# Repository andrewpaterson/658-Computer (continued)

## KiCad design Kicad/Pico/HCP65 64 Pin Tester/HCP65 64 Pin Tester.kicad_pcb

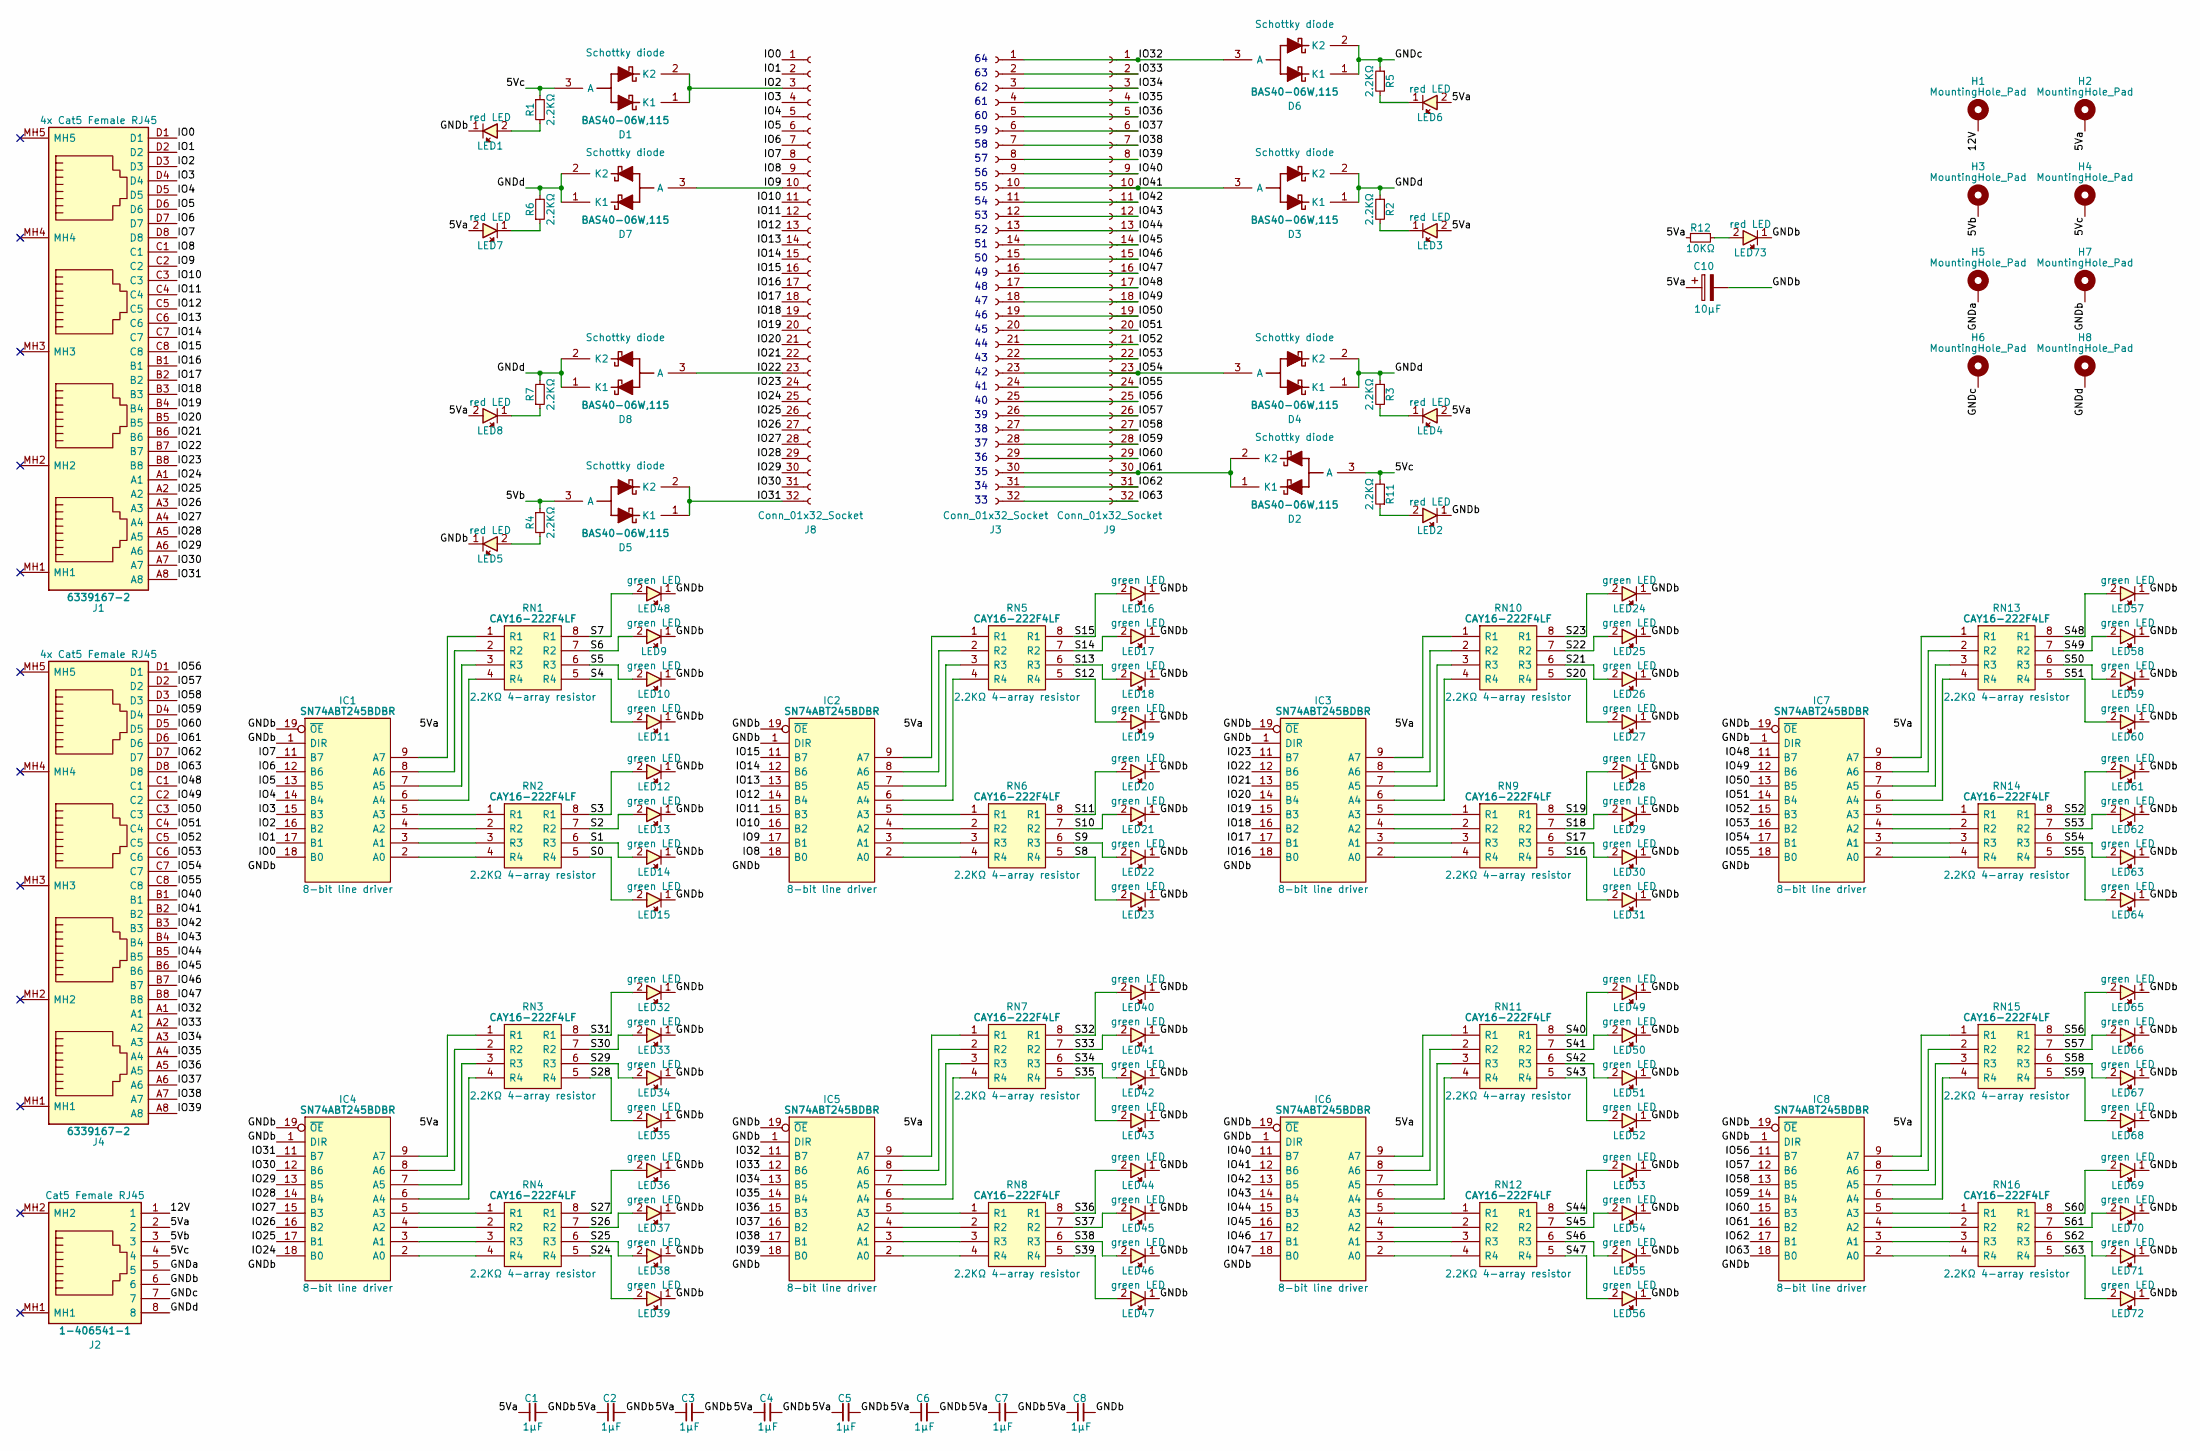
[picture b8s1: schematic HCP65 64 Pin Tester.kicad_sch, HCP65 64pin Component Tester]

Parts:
C1, C2, C3, C4, C5, C6, C7, C8: 1μF; C_0805
C10: 10μF; CP_Radial_D4.0mm_P2.00mm
D1, D2, D3, D4, D5, D6, D7, D8: BAS40-06W,115; SOT65P210X110-3N; Manufacturer_Part_Number BAS40-06W,115; Mouser Part Number 771-BAS40-06W115
H1, H2, H3, H4, H5, H6, H7, H8: MountingHole_Pad; MountingHole_3.2mm_M3_Pad
IC1, IC2, IC3, IC4, IC5, IC6, IC7, IC8: SN74ABT245BDBR; SOP65P780X200-20N; Manufacturer_Part_Number SN74ABT245BDBR; Mouser Part Number 595-SN74ABT245BDBR
J1, J4: 6339167-2; 63391672; Manufacturer_Part_Number 6339167-2; Mouser Part Number 571-6339167-2
J2: 1-406541-1; 1-406541-1_1; Manufacturer_Part_Number 1-406541-1; Mouser Part Number 571-1-406541-1
J3, J8, J9: Conn_01x32_Socket; PinSocket_1x32_P2.54mm_Vertical
LED1, LED2, LED3, LED4, LED5, LED6, LED7, LED8, LED73: 150224SS73100; 150224SS73100A; Manufacturer_Part_Number 150224SS73100; Mouser Part Number 710-150224SS73100
LED9, LED10, LED11, LED12, LED13, LED14, LED15, LED16, LED17, LED18, LED19, LED20, LED21, LED22, LED23, LED24, LED25, LED26, LED27, LED28, LED29, LED30, LED31, LED32, LED33, LED34, LED35, LED36, LED37, LED38, LED39, LED40, LED41, LED42, LED43, LED44, LED45, LED46, LED47, LED48, LED49, LED50, LED51, LED52, LED53, LED54, LED55, LED56, LED57, LED58, LED59, LED60, LED61, LED62, LED63, LED64, LED65, LED66, LED67, LED68, LED69, LED70, LED71, LED72: 150224VS73100A; Manufacturer_Part_Number 150224VS73100A; Mouser Part Number 710-150224VS73100A
R1, R2, R3, R4, R5, R6, R7, R11: 2.2KΩ; R_0805
R12: 10KΩ; R_0805
RN1, RN2, RN3, RN4, RN5, RN6, RN7, RN8, RN9, RN10, RN11, RN12, RN13, RN14, RN15, RN16: CAY16-222F4LF; CAY16-J4; Manufacturer_Part_Number CAY16-222F4LF; Mouser Part Number 652-CAY16-2201F4LF

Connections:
/5Va: C1.1, C2.1, C3.1, C4.1, C5.1, C6.1, C7.1, C8.1, C10.1, H2.1, IC1.20 (5V), IC2.20 (5V), IC3.20 (5V), IC4.20 (5V), IC5.20 (5V), IC6.20 (5V), IC7.20 (5V), IC8.20 (5V), J2.2, LED3.2, LED4.2, LED6.2, LED7.2, LED8.2, R12.1
/5Vb: D5.3 (A), H3.1, J2.3, R4.1
/5Vc: D1.3 (A), D2.3 (A), H4.1, J2.4, R1.1, R11.2
/12V: H1.1, J2.1
/GNDa: H5.1, J2.5
/GNDb: C1.2, C2.2, C3.2, C4.2, C5.2, C6.2, C7.2, C8.2, C10.2, H7.1, IC1.1 (DIR), IC1.10 (GND), IC1.19 (~OE), IC2.1 (DIR), IC2.10 (GND), IC2.19 (~OE), IC3.1 (DIR), IC3.10 (GND), IC3.19 (~OE), IC4.1 (DIR), IC4.10 (GND), IC4.19 (~OE), IC5.1 (DIR), IC5.10 (GND), IC5.19 (~OE), IC6.1 (DIR), IC6.10 (GND), IC6.19 (~OE), IC7.1 (DIR), IC7.10 (GND), IC7.19 (~OE), IC8.1 (DIR), IC8.10 (GND), IC8.19 (~OE), J2.6, LED1.1, LED2.1, LED5.1, LED9.1, LED10.1, LED11.1, LED12.1, LED13.1, LED14.1, LED15.1, LED16.1, LED17.1, LED18.1, LED19.1, LED20.1, LED21.1, LED22.1, LED23.1, LED24.1, LED25.1, LED26.1, LED27.1, LED28.1, LED29.1, LED30.1, LED31.1, LED32.1, LED33.1, LED34.1, LED35.1, LED36.1, LED37.1, LED38.1, LED39.1, LED40.1, LED41.1, LED42.1, LED43.1, LED44.1, LED45.1, LED46.1, LED47.1, LED48.1, LED49.1, LED50.1, LED51.1, LED52.1, LED53.1, LED54.1, LED55.1, LED56.1, LED57.1, LED58.1, LED59.1, LED60.1, LED61.1, LED62.1, LED63.1, LED64.1, LED65.1, LED66.1, LED67.1, LED68.1, LED69.1, LED70.1, LED71.1, LED72.1, LED73.1
/GNDc: D6.1 (K1), D6.2 (K2), H6.1, J2.7, R5.1
/GNDd: D3.1 (K1), D3.2 (K2), D4.1 (K1), D4.2 (K2), D7.1 (K1), D7.2 (K2), D8.1 (K1), D8.2 (K2), H8.1, J2.8, R2.1, R3.1, R6.2, R7.2
/IO0: IC1.18 (B0), J1.D1, J8.1
/IO1: IC1.17 (B1), J1.D2, J8.2
/IO2: D1.1 (K1), D1.2 (K2), IC1.16 (B2), J1.D3, J8.3
/IO3: IC1.15 (B3), J1.D4, J8.4
/IO4: IC1.14 (B4), J1.D5, J8.5
/IO5: IC1.13 (B5), J1.D6, J8.6
/IO6: IC1.12 (B6), J1.D7, J8.7
/IO7: IC1.11 (B7), J1.D8, J8.8
/IO8: IC2.18 (B0), J1.C1, J8.9
/IO9: D7.3 (A), IC2.17 (B1), J1.C2, J8.10
/IO10: IC2.16 (B2), J1.C3, J8.11
/IO11: IC2.15 (B3), J1.C4, J8.12
/IO12: IC2.14 (B4), J1.C5, J8.13
/IO13: IC2.13 (B5), J1.C6, J8.14
/IO14: IC2.12 (B6), J1.C7, J8.15
/IO15: IC2.11 (B7), J1.C8, J8.16
/IO16: IC3.18 (B0), J1.B1, J8.17
/IO17: IC3.17 (B1), J1.B2, J8.18
/IO18: IC3.16 (B2), J1.B3, J8.19
/IO19: IC3.15 (B3), J1.B4, J8.20
/IO20: IC3.14 (B4), J1.B5, J8.21
/IO21: IC3.13 (B5), J1.B6, J8.22
/IO22: D8.3 (A), IC3.12 (B6), J1.B7, J8.23
/IO23: IC3.11 (B7), J1.B8, J8.24
/IO24: IC4.18 (B0), J1.A1, J8.25
/IO25: IC4.17 (B1), J1.A2, J8.26
/IO26: IC4.16 (B2), J1.A3, J8.27
/IO27: IC4.15 (B3), J1.A4, J8.28
/IO28: IC4.14 (B4), J1.A5, J8.29
/IO29: IC4.13 (B5), J1.A6, J8.30
/IO30: IC4.12 (B6), J1.A7, J8.31
/IO31: D5.1 (K1), D5.2 (K2), IC4.11 (B7), J1.A8, J8.32
/IO32: D6.3 (A), IC5.11 (B7), J3.1, J4.A1, J9.1
/IO33: IC5.12 (B6), J3.2, J4.A2, J9.2
/IO34: IC5.13 (B5), J3.3, J4.A3, J9.3
/IO35: IC5.14 (B4), J3.4, J4.A4, J9.4
/IO36: IC5.15 (B3), J3.5, J4.A5, J9.5
/IO37: IC5.16 (B2), J3.6, J4.A6, J9.6
/IO38: IC5.17 (B1), J3.7, J4.A7, J9.7
/IO39: IC5.18 (B0), J3.8, J4.A8, J9.8
/IO40: IC6.11 (B7), J3.9, J4.B1, J9.9
/IO41: D3.3 (A), IC6.12 (B6), J3.10, J4.B2, J9.10
/IO42: IC6.13 (B5), J3.11, J4.B3, J9.11
/IO43: IC6.14 (B4), J3.12, J4.B4, J9.12
/IO44: IC6.15 (B3), J3.13, J4.B5, J9.13
/IO45: IC6.16 (B2), J3.14, J4.B6, J9.14
/IO46: IC6.17 (B1), J3.15, J4.B7, J9.15
/IO47: IC6.18 (B0), J3.16, J4.B8, J9.16
/IO48: IC7.11 (B7), J3.17, J4.C1, J9.17
/IO49: IC7.12 (B6), J3.18, J4.C2, J9.18
/IO50: IC7.13 (B5), J3.19, J4.C3, J9.19
/IO51: IC7.14 (B4), J3.20, J4.C4, J9.20
/IO52: IC7.15 (B3), J3.21, J4.C5, J9.21
/IO53: IC7.16 (B2), J3.22, J4.C6, J9.22
/IO54: D4.3 (A), IC7.17 (B1), J3.23, J4.C7, J9.23
/IO55: IC7.18 (B0), J3.24, J4.C8, J9.24
/IO56: IC8.11 (B7), J3.25, J4.D1, J9.25
/IO57: IC8.12 (B6), J3.26, J4.D2, J9.26
/IO58: IC8.13 (B5), J3.27, J4.D3, J9.27
/IO59: IC8.14 (B4), J3.28, J4.D4, J9.28
/IO60: IC8.15 (B3), J3.29, J4.D5, J9.29
/IO61: D2.1 (K1), D2.2 (K2), IC8.16 (B2), J3.30, J4.D6, J9.30
/IO62: IC8.17 (B1), J3.31, J4.D7, J9.31
/IO63: IC8.18 (B0), J3.32, J4.D8, J9.32
/S0: LED15.2, RN2.5 (R4)
/S1: LED14.2, RN2.6 (R3)
/S2: LED13.2, RN2.7 (R2)
/S3: LED12.2, RN2.8 (R1)
/S4: LED11.2, RN1.5 (R4)
/S5: LED10.2, RN1.6 (R3)
/S6: LED9.2, RN1.7 (R2)
/S7: LED48.2, RN1.8 (R1)
/S8: LED23.2, RN6.5 (R4)
/S9: LED22.2, RN6.6 (R3)
/S10: LED21.2, RN6.7 (R2)
/S11: LED20.2, RN6.8 (R1)
/S12: LED19.2, RN5.5 (R4)
/S13: LED18.2, RN5.6 (R3)
/S14: LED17.2, RN5.7 (R2)
/S15: LED16.2, RN5.8 (R1)
/S16: LED31.2, RN9.5 (R4)
/S17: LED30.2, RN9.6 (R3)
/S18: LED29.2, RN9.7 (R2)
/S19: LED28.2, RN9.8 (R1)
/S20: LED27.2, RN10.5 (R4)
/S21: LED26.2, RN10.6 (R3)
/S22: LED25.2, RN10.7 (R2)
/S23: LED24.2, RN10.8 (R1)
/S24: LED39.2, RN4.5 (R4)
/S25: LED38.2, RN4.6 (R3)
/S26: LED37.2, RN4.7 (R2)
/S27: LED36.2, RN4.8 (R1)
/S28: LED35.2, RN3.5 (R4)
/S29: LED34.2, RN3.6 (R3)
/S30: LED33.2, RN3.7 (R2)
/S31: LED32.2, RN3.8 (R1)
/S32: LED40.2, RN7.8 (R1)
/S33: LED41.2, RN7.7 (R2)
/S34: LED42.2, RN7.6 (R3)
/S35: LED43.2, RN7.5 (R4)
/S36: LED44.2, RN8.8 (R1)
/S37: LED45.2, RN8.7 (R2)
/S38: LED46.2, RN8.6 (R3)
/S39: LED47.2, RN8.5 (R4)
/S40: LED49.2, RN11.8 (R1)
/S41: LED50.2, RN11.7 (R2)
/S42: LED51.2, RN11.6 (R3)
/S43: LED52.2, RN11.5 (R4)
/S44: LED53.2, RN12.8 (R1)
/S45: LED54.2, RN12.7 (R2)
/S46: LED55.2, RN12.6 (R3)
/S47: LED56.2, RN12.5 (R4)
/S48: LED57.2, RN13.8 (R1)
/S49: LED58.2, RN13.7 (R2)
/S50: LED59.2, RN13.6 (R3)
/S51: LED60.2, RN13.5 (R4)
/S52: LED61.2, RN14.8 (R1)
/S53: LED62.2, RN14.7 (R2)
/S54: LED63.2, RN14.6 (R3)
/S55: LED64.2, RN14.5 (R4)
/S56: LED65.2, RN15.8 (R1)
/S57: LED66.2, RN15.7 (R2)
/S58: LED67.2, RN15.6 (R3)
/S59: LED68.2, RN15.5 (R4)
/S60: LED69.2, RN16.8 (R1)
/S61: LED70.2, RN16.7 (R2)
/S62: LED71.2, RN16.6 (R3)
/S63: LED72.2, RN16.5 (R4)
unnamed: IC1.2 (A0), RN2.4 (R4)
unnamed: IC1.3 (A1), RN2.3 (R3)
unnamed: IC1.4 (A2), RN2.2 (R2)
unnamed: IC1.5 (A3), RN2.1 (R1)
unnamed: IC1.6 (A4), RN1.4 (R4)
unnamed: IC1.7 (A5), RN1.3 (R3)
unnamed: IC1.8 (A6), RN1.2 (R2)
unnamed: IC1.9 (A7), RN1.1 (R1)
unnamed: IC2.2 (A0), RN6.4 (R4)
unnamed: IC2.3 (A1), RN6.3 (R3)
unnamed: IC2.4 (A2), RN6.2 (R2)
unnamed: IC2.5 (A3), RN6.1 (R1)
unnamed: IC2.6 (A4), RN5.4 (R4)
unnamed: IC2.7 (A5), RN5.3 (R3)
unnamed: IC2.8 (A6), RN5.2 (R2)
unnamed: IC2.9 (A7), RN5.1 (R1)
unnamed: IC3.2 (A0), RN9.4 (R4)
unnamed: IC3.3 (A1), RN9.3 (R3)
unnamed: IC3.4 (A2), RN9.2 (R2)
unnamed: IC3.5 (A3), RN9.1 (R1)
unnamed: IC3.6 (A4), RN10.4 (R4)
unnamed: IC3.7 (A5), RN10.3 (R3)
unnamed: IC3.8 (A6), RN10.2 (R2)
unnamed: IC3.9 (A7), RN10.1 (R1)
unnamed: IC4.2 (A0), RN4.4 (R4)
unnamed: IC4.3 (A1), RN4.3 (R3)
unnamed: IC4.4 (A2), RN4.2 (R2)
unnamed: IC4.5 (A3), RN4.1 (R1)
unnamed: IC4.6 (A4), RN3.4 (R4)
unnamed: IC4.7 (A5), RN3.3 (R3)
unnamed: IC4.8 (A6), RN3.2 (R2)
unnamed: IC4.9 (A7), RN3.1 (R1)
unnamed: IC5.2 (A0), RN8.4 (R4)
unnamed: IC5.3 (A1), RN8.3 (R3)
unnamed: IC5.4 (A2), RN8.2 (R2)
unnamed: IC5.5 (A3), RN8.1 (R1)
unnamed: IC5.6 (A4), RN7.4 (R4)
unnamed: IC5.7 (A5), RN7.3 (R3)
unnamed: IC5.8 (A6), RN7.2 (R2)
unnamed: IC5.9 (A7), RN7.1 (R1)
unnamed: IC6.2 (A0), RN12.4 (R4)
unnamed: IC6.3 (A1), RN12.3 (R3)
unnamed: IC6.4 (A2), RN12.2 (R2)
unnamed: IC6.5 (A3), RN12.1 (R1)
unnamed: IC6.6 (A4), RN11.4 (R4)
unnamed: IC6.7 (A5), RN11.3 (R3)
unnamed: IC6.8 (A6), RN11.2 (R2)
unnamed: IC6.9 (A7), RN11.1 (R1)
unnamed: IC7.2 (A0), RN14.4 (R4)
unnamed: IC7.3 (A1), RN14.3 (R3)
unnamed: IC7.4 (A2), RN14.2 (R2)
unnamed: IC7.5 (A3), RN14.1 (R1)
unnamed: IC7.6 (A4), RN13.4 (R4)
unnamed: IC7.7 (A5), RN13.3 (R3)
unnamed: IC7.8 (A6), RN13.2 (R2)
unnamed: IC7.9 (A7), RN13.1 (R1)
unnamed: IC8.2 (A0), RN16.4 (R4)
unnamed: IC8.3 (A1), RN16.3 (R3)
unnamed: IC8.4 (A2), RN16.2 (R2)
unnamed: IC8.5 (A3), RN16.1 (R1)
unnamed: IC8.6 (A4), RN15.4 (R4)
unnamed: IC8.7 (A5), RN15.3 (R3)
unnamed: IC8.8 (A6), RN15.2 (R2)
unnamed: IC8.9 (A7), RN15.1 (R1)
unnamed: LED1.2, R1.2
unnamed: LED2.2, R11.1
unnamed: LED3.1, R2.2
unnamed: LED4.1, R3.2
unnamed: LED5.2, R4.2
unnamed: LED6.1, R5.2
unnamed: LED7.1, R6.1
unnamed: LED8.1, R7.1
unnamed: LED73.2, R12.2

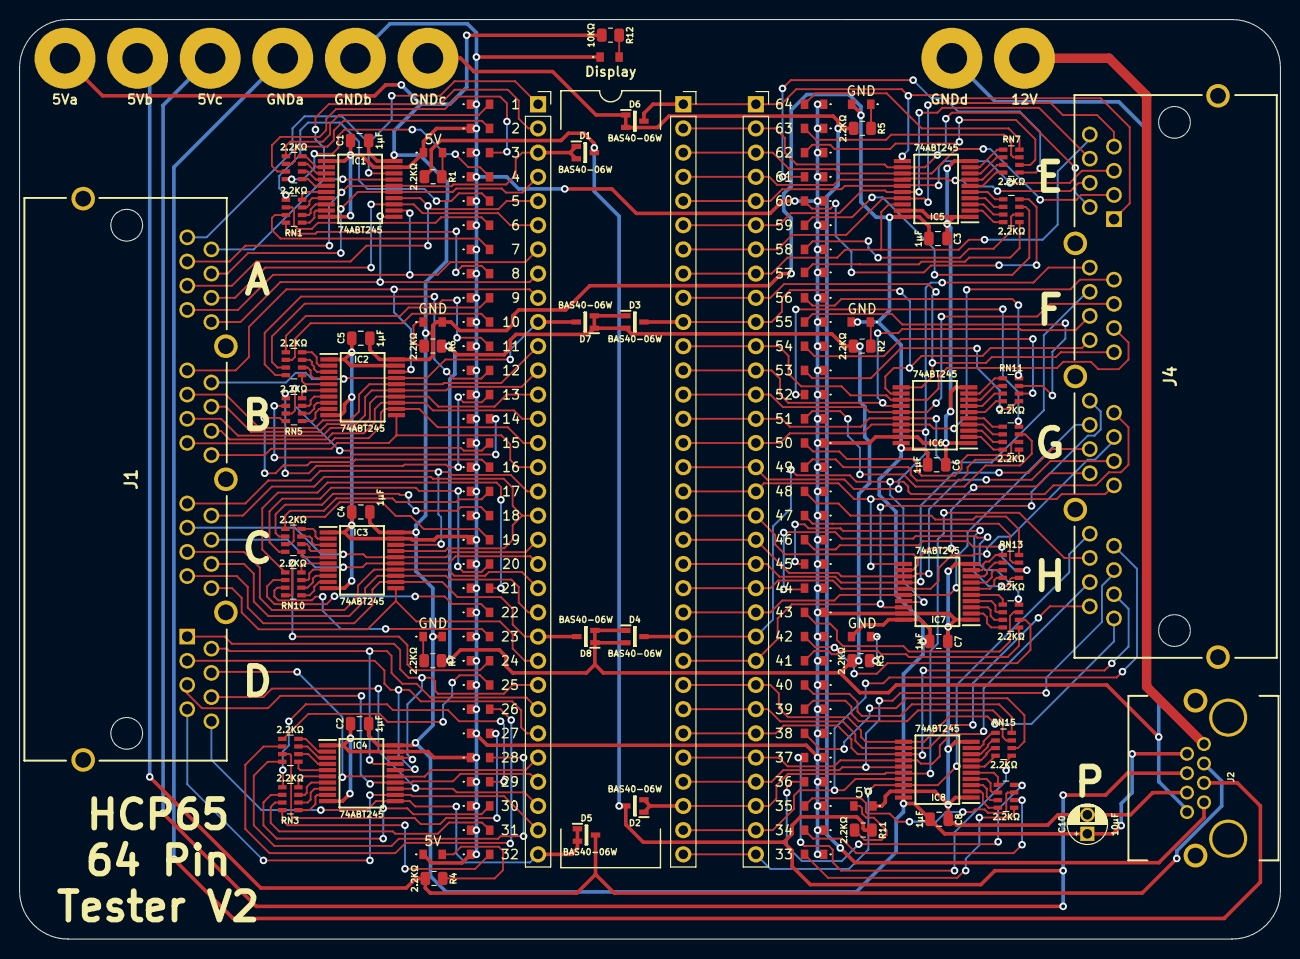
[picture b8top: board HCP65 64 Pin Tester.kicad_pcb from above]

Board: 2 copper layers, 132.4 x 96.5 mm, 137 parts (0 on the bottom side), 209 nets.

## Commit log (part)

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2025-03-09 More cleanup on the Processor Board.
2025-03-12 Include Valid Address in address decoding.
2025-03-12 Deleted Wide Interrupts and Wide Address Decode.
2025-03-13 Fixed RAM and ROM selects not swapping before native mode.
2025-03-14 Added LCD tester boards.
2025-03-14 Auto-routed LCD Dual 7 Segment tester PCB.
2025-03-14 Cleaned up LCD Dual 7 Segment Display.
2025-03-14 Added a TSSOP32 adapter.
2025-03-15 Auto-routed LCD 14 Segment tester PCB.
2025-03-15 Cleaned up LCD 14 Segment Display.
2025-03-15 Added DIP switches to test LCD boards.
2025-03-16 Updated DIP to TSSOP adapter model.
2025-03-19 Bit more clean up on the Processor Board.
2025-03-20 Moved and labeled Mainboard Small pull resistors.
2025-03-20 Nothing in particular. Just curious how generating the exact same Gerbers would differ.
2025-04-21 Bunch of stuff I forgot to commit. Basically re-doing the PICO programmer / analyser.
2025-04-23 Power and Reset board.
2025-04-24 Removed GPIO filtering and rounded traces.
2025-04-24 Routed a 32bit GPIO Board.
2025-04-24 Updated Processor Board LD1117.
2025-04-26 Signal Protection and GPIO Power Switch.
2025-04-26 Reset the 40pin blank symbol.
2025-04-26 Added GPIO Bus.
2025-04-26 Removed Pico Wide.
2025-04-26 Autorouted GPIO 32bit Board.
2025-04-27 Cleaned up GPIO Controller Board.
2025-04-27 Cleaned up GPIO 32bit Board.
2025-04-27 Added GPIO Backplan Board.
2025-04-27 Unrouted the GPIO Backplane Board.
2025-04-27 Reautorouted the GPIO Backplane Board.
2025-04-27 Cleaned up GPIO Backplane.
2025-04-27 Fixed Signal Protection order on 32bit board.
2025-04-28 Lots of random stuff.
2025-05-04 Bit of cleanup in W65C816 simulator.
2025-05-06 I think I mostly fixed the GPIO Power Switch.
2025-05-06 Found a fixed version of the W65C816 Programming Manual.
2025-05-06 Cleaned up a lot of silkscreens.
2025-05-07 Partially added some Operations.
2025-05-08 Completed W65C816State.
2025-05-11 Stop passing the simulation around when only the timeline is needed.
2025-05-22 I don't remember what I did.
2025-05-24 Flipped pins in 4x RJ45 connector.
2025-05-26 Added filtering to the GPIO Address Decode board.
2025-06-05 Cleaned up the Video DAC slightly.
2025-06-08 Converted GPIO Backplane board to Kicad 9.0
2025-06-08 Converted all GPIO boards to Kicad 9.0
2025-06-08 Converted Programmers to Kicad 9.0
2025-06-15 Added 74LVC2T45 datasheet.
2025-06-15 Converted Processor Board to Kicad 9.0
2025-06-15 Added a Coprocessor Memory board.
2025-06-16 Renamed Coprocessor Memory board to Memory 1MB.
2025-06-16 Cleaned up Memory 4MB routing.
2025-06-16 Added W65C816 Minimal and Memory 1MB symbols and footrpints.
2025-06-16 Fixed 3D model directories.
2025-06-16 Added Coprocessor Board and shrunk W65C816 Latch.
2025-06-17 Lots and lots of Coprocessor boards,
2025-06-18 Deleeted Coprocessor Board.
2025-06-18 Auto routed Coprocessor Board - Additional.
2025-06-18 Manually routing Coprocessor Board - Additional.
2025-06-18 Auto routed Coprocessor Board - Main.
2025-06-18 Un-routed Coprocessor Board - Main.
2025-06-18 Un-routed Coprocessor Board - Additional.
2025-06-19 Split some Processor Board sub boards into multiple parts.
2025-06-19 Nicenend up the Coprocessor Board - Main a bit.
2025-06-20 Ray traced the Coprocessor Board - Main.
2025-06-20 Generated Coprocessor Board - Main Gerbers.
2025-06-20 Converted Device Decode Stage A and B to Kicad 9.0
2025-06-20 Manually routed the Coprocessor Board - Additional.
2025-06-25 Re-did Mainboard power supply.
2025-06-25 Converted Processor Board to Kicad 9.0 (again).
2025-06-25 Cleaned up the Processor Board PCB even more.
2025-06-25 Converted W65C816 Clock Hold to Kicad 9.0.
2025-06-26 Converted W65C816 Opcode Display to Kicad 9.0.
2025-06-26 Converted HCP65 Single MPU Board to Kicad 9.0.
2025-06-26 Converted HCP65 Processor Boards to Kicad 9.0.
2025-06-26 Converted HCP65 LCD Boards to Kicad 9.0.
2025-06-27 Added RAM 48K Select.
2025-06-27 Re-routed RAM 48K Select.
2025-06-27 Converted LCD testers to Kicad 9.0.
2025-06-27 Converted a whole lot of boards to Kicad 9.0
2025-07-03 Converted Triple Clock Generator to Kicad 9.0.
2025-07-03 Converted Quad Clock Generator to Kicad 9.0.
2025-07-03 Converted Main Memory Select to Kicad 9.0.
2025-07-03 Converted Main Memory Enable to Kicad 9.0.
2025-07-03 Converted Main Memory Abort to Kicad 9.0.
2025-07-06 Fixed quad RJ45 connector footprint and Signal Protection symbol.
2025-07-14 Used 3W Zener diodes for signal protection.
2025-07-18 Converted GPIO 16bit to Kicad 9.0.
2025-08-17 40 Pin component tester PCB.
2025-08-18 40 Pin component tester PCB redo.
2025-08-18 Auto-routed 40 Pin component tester PCB.
2025-08-18 56 Pin component tester schematic.
2025-08-19 36 Pin component tester schematic.
2025-08-19 Auto-routed 32 Pin component tester PCB.
2025-08-19 Auto-routed 24 Pin component tester PCB.
2025-08-19 Manually routing the 40pin Tester.
2025-08-20 Failed to Auto-route 64 Pin component tester PCB.
2025-08-20 Manually routing the 56pin Tester.
2025-08-21 Un-routed the 64pin Tester.
2025-08-21 Auto-routed the 64pin Tester.
2025-08-21 Generated Gerbers for 24pin Tester.
2025-08-21 Generated Gerbers for 32pin Tester.
2025-08-21 Generated Gerbers for 40pin Tester.
2025-08-21 Generated Gerbers for 56pin Tester.
2025-08-22 Renamed HCP65 24 Pin Tester.
2025-08-22 Upgraded to Kicad 9.0.
2025-08-22 Added an 8bit adder.
2025-08-22 Changed the Graphics Board adder from 16 to 24bits.
2025-08-22 Upgraded Audio Board to Kicad 9.0.
2025-08-23 Upgraded all Compnent Boards to Kicad 9.0.
2025-08-23 Upgraded LCD Board to Kicad 9.0.
2025-08-23 Regenerated all Main Clock boards
2025-08-23 Upgraded UART Boards to Kicad 9.0.
2025-08-23 Upgraded VIA Boards to Kicad 9.0.
2025-08-23 Buffered Video Memory signals.
2025-08-23 Upgraded Video Boards to Kicad 9.0.
2025-08-24 Generated Memory Board Gerbers.
2025-08-27 Added board alignment silk screen to 24- 32- and 40 pin tester boards.
2025-08-27 Added board alignment silk screen to 56- and 64 pin tester boards.
2025-09-04 Fixed MPU Address Decode.
2025-09-10 Tester board power names.
2025-09-12 Stop USB 5V from powering the whole device.
2025-09-13 Added debug points to Tester boards.
2025-09-13 Moved Component Tester into Old.
2025-09-16 Random changes.
2025-09-16 Added Main Memory Small Abort.
2025-09-17 Drive failure.
2025-09-18 Routed Processor Full Device.
2025-09-19 Fixed Processor Board silkscreen.
2025-09-19 Fixed HCP65 footprint silkscreens.
2025-09-19 Added Processor Control Full Device.
2025-09-19 Added Processor Control Small Device.
2025-09-19 Added processor control to Mainboard Full.
2025-09-19 Added Processor Reset Device.
2025-09-20 Silkscreen for Processor Full Device.
2025-09-20 Renamed Main Memory Abort to Main Memory Full Abort.
2025-09-20 Added Processor Reset Device to Mainboard Small.
2025-09-20 Remove reset circuitry from Clock Generators.
2025-09-20 Deleted dual and quad clock generators.
2025-09-20 Removed reset from Triple clock generator.
2025-09-20 Rerouted Mainboard Small.
2025-09-21 Removed 12V from clock and status devices.
2025-09-21 Added a panic button to the Mainboard Full.
2025-09-21 Auto routed the Mainboard Full board.
2025-09-21 Routed Mainboard Small (again).
2025-09-22 Stretched the Mainboard Small.
2025-09-22 Routed some of the Mainboard Full.
2025-09-23 Finished routing the Mainboard Full.
2025-09-24 Buses and fixes on the Video Board - Memory.
2025-09-25 Added (some) buses to Video Board - Memory.
2025-09-27 Cleaned up Video Board signals PCB.
2025-09-27 Cleaning up the Video Board memory PCB.
2025-09-28 Refactored Video Board Memory schematic.
2025-09-28 Generated Video schematic PDFs.
2025-09-29 Added component board symbols and 3D models.
2025-09-29 Use Board symbols in schematics.
2025-10-01 Added stabilisation pins to the Opcode Display board.
2025-10-01 Added more silkscreen to the Debug Display board.
2025-10-04 Swapped Mainboard Full device socket positions.
2025-10-08 Cleaned up Address Decode schematics.
2025-10-08 Cleaned up Blitter Board schematics.
2025-10-10 Renaming buses.
2025-10-10 Renamed buses with subscripts.
2025-10-10 Started generating the Main signal for Graphics.
2025-10-12 Miscellaneous cleanup.
2025-10-12 Generated Video Board schematic PDFs.
2025-10-12 Rerouted UART Board.
2025-10-12 Minor cleanup on Coprocessor boards.
2025-10-14 WinCUPL II project.
2025-10-14 Setting up Kicad under Linux
2025-10-15 Cleaning up the Audio Board.
2025-10-15 Deleted all fp-info-caches.
2025-10-17 Regenerated MPU Address Decode gerbers.
2025-10-17 Regenerate all support gerbers for fabrication.
2025-10-24 Fixed a clearance violation.
2025-10-24 Fixed another clearance violation
2025-11-10 Something about the 56 Pin Tester.
2025-11-14 Added a bunch of notes and routed the Kernal Mode flip-flop.
2025-11-19 Something to do with the Coprocessor Board.
2025-12-04 Cleaned up W65C816 Minimal tracks slightly.
2026-01-01 Changed the visible layers.
2026-01-05 Started fixing 24, 32 and 40 pin Tester Boards.
2026-01-10 I don't know what I was doing.
2026-01-10 Fixed 56 and 64 pin Tester Boards.
2026-01-11 Fixed 24pin Tester board.
2026-01-12 Fixed 32pin Tester Board.
2026-01-12 Fixed 40pin Tester Board.
2026-01-13 Audio and Coprocessor boards with proper board schematic symbol and global labels.
2026-01-14 Main boards with proper board schematic symbol and global labels.
2026-01-14 Processor boards with proper board schematic symbol and global labels.
2026-01-14 PS2 and SD Card boards with proper board schematic symbol and global labels.
2026-01-14 SNES Controller, UART and VIA boards with proper schematics and global labels.
2026-01-16 Generate Tester Gerbers for V2 fabrication.
2026-01-16 Generate LCD Gerbers for fabrication.
2026-01-18 Added filterers to Address Decode and rerouted Processor Board for wider Address Decode.
2026-01-19 Cleaned up Processor Board routing and generated Gerbers.
2026-01-19 Rerouted Coprocessor Additional Board.
2026-01-20 Rerouted Graphics Board.
2026-01-20 Rerouted Audio Board.
2026-01-20 Rerouted Video Signals and Memory Boards.
2026-01-21 Regenerated Mainboard Gerbers.
2026-01-22 Bit more cleanup on Coprocessor boards.
2026-01-24 Video Main Address and Data buffering.
2026-01-24 Ignore Main Buffer backups.
2026-01-25 Undid Video Main buffering.
2026-01-27 Installed Courier New font.
2026-01-28 Added inputs and outputs to the Processor Board schematic.
2026-01-28 Fixed Kernal Board symbol and Processor Board. Whoops.
2026-01-31 Routed board presence reader on the Processor Board.
2026-01-31 Completed Board Presence routing.
2026-02-05 Fixed Clock Hold resetting the counter too early.
2026-02-05 index on master: 6986ae575 Completed Board Presence routing.
2026-02-12 Random fix to SubcircuitView.
2026-02-13 Added a D-type flip flop integrated circuit.
2026-02-14 Added a Probe integrated circuit.
2026-02-15 Renamed Counter to IdentifierSource.
2026-02-15 Added a Counter integrated circuit.
2026-02-16 Return trace list as set.
2026-02-16 Fixed port trace WireTraceConverter.
2026-02-19 Added a watchdog timer clock to the main board.
2026-02-19 Added a Hold Count board.
2026-02-19 Hold logic.
2026-02-19 Split Clock Hold into two Hold Count and Clock Hold.
2026-02-21 Manually routing the Processor Board.
2026-02-23 Finished manually routing the Processor Board.
2026-02-24 Cleaning routing on the Processor Board.
2026-02-25 Added a Clock Hold V1 to V2 converter board.
2026-02-25 Cleaned up address decode routing.
2026-02-26 Deleted HCP65 Single MPU Board.
2026-03-03 Something about the SD card schematics.
2026-03-03 Updated Coprocessor Board for updated power supply.
2026-03-04 Added a UART signals board that removes that SMD components from the UART board.
2026-03-04 Use UART signals board.
2026-03-04 Deleted all boards by accident. Started setting up blank boards.
2026-03-04 Re-added pin model boards.
2026-03-04 Added silkscreen and power components to some blank boards.
2026-03-04 Added some more blank board projects.
2026-03-04 Added all blank board projects.
2026-03-04 Fixed up UART signals and board.
2026-04-28 Auto stash before rebase of "master" onto "origin/master"
    Cleaned up Address Decode slightly.
